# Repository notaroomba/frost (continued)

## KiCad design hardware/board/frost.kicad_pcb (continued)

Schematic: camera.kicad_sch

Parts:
C135: 1uF X5R 6.3V; C_0402_1005Metric
C136, C141, C142, C145, C146: 100nF X5R 10V; C_0402_1005Metric
C137: 22pF C0G 50V; C_0402_1005Metric
C138, C143, C144: 10uF X5R 10V; C_0603_1608Metric
C139, C140: 4.7uF X5R 6.3V; C_0603_1608Metric
C360, C361: 100nF X5R 10V; C_0201_0603Metric
R76: 10K 5%; R_0402_1005Metric
R77: 200K 1%; R_0402_1005Metric
R78: 390K 1%; R_0402_1005Metric
R79, R80, R81: 0R 5%; R_0402_1005Metric
U1: RK3568; BGA636C65P28X28_1900X1900X168; PARTREV 1.3; LCSC C3345225
U26: LP3983SAB5F-08; SOT-23-5_L3.0-W1.7-P0.95-LS2.8-BR; LCSC Part C324567
U27: 5054133410_C6422029; CONN-SMD_5054133410; LCSC Part C6422029

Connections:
CAM_CLKOUT0: U27.29
DVP_PWREN0_H_GPIO0_D3: R76.1; also elsewhere on the board
I2C2_SCL_M1: U27.31; also elsewhere on the board
I2C2_SDA_M1: U27.32; also elsewhere on the board
MIPI_AVDD_0V9: C360.1, U1.W14 (MIPI_CSI_RX_AVDD_0V9); also elsewhere on the board
MIPI_AVDD_1V8: C361.1, U1.Y14 (MIPI_CSI_RX_AVDD_1V8); also elsewhere on the board
MIPI_CAM0_RST_L_GPIO3_C6: R81.2; also elsewhere on the board
MIPI_CSI_RX_CLK0N: U1.AH10 (MIPI_CSI_RX_CLK0N), U27.10
MIPI_CSI_RX_CLK0P: U1.AG10 (MIPI_CSI_RX_CLK0P), U27.9
MIPI_CSI_RX_CLK1N: U1.AH9 (MIPI_CSI_RX_CLK1N)
MIPI_CSI_RX_CLK1P: U1.AG9 (MIPI_CSI_RX_CLK1P)
MIPI_CSI_RX_D0N: U1.AH12 (MIPI_CSI_RX_D0N), U27.7
MIPI_CSI_RX_D0P: U1.AG12 (MIPI_CSI_RX_D0P), U27.6
MIPI_CSI_RX_D1N: U1.AH11 (MIPI_CSI_RX_D1N), U27.13
MIPI_CSI_RX_D1P: U1.AG11 (MIPI_CSI_RX_D1P), U27.12
MIPI_CSI_RX_D2N: U1.AD11 (MIPI_CSI_RX_D2N), U27.4
MIPI_CSI_RX_D2P: U1.AE11 (MIPI_CSI_RX_D2P), U27.3
MIPI_CSI_RX_D3N: U1.AE9 (MIPI_CSI_RX_D3N), U27.16
MIPI_CSI_RX_D3P: U1.AD9 (MIPI_CSI_RX_D3P), U27.15
MIPI_CSI_X4_RST: C146.1, R81.1, U27.26
unnamed: C137.2, R77.1, R78.2, U26.4 (ADJ)
unnamed: C136.1, R76.2, U26.3 (CE)
VCC1V8_DOVDD_DVP: C139.1, C141.1, R79.1, U27.22
VCC2V8_AVDD_DVP: U27.23
VCC2V8_DVP: C140.1, C144.1, C145.1, R80.1, U27.24
VCC3V3_SYS: C135.1, U26.1 (VIN); also elsewhere on the board
VCCA1V8_IMAGE_P: R79.2; also elsewhere on the board
VDD1V2_DVDD_DVP: C137.1, C138.1, C142.1, C143.1, R77.2, U26.5 (VOUT), U27.21
VDDA0V9_IMAGE_P: R80.2; also elsewhere on the board

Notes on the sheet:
Frost
Camera MIPI Connector
RK3568
Diff 100 Ohm ±10%
Close to FPC Connector
NEEDS REWORKING TO ANOTHER STANDARD (JETSON NANO)
Power / Decoupling

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
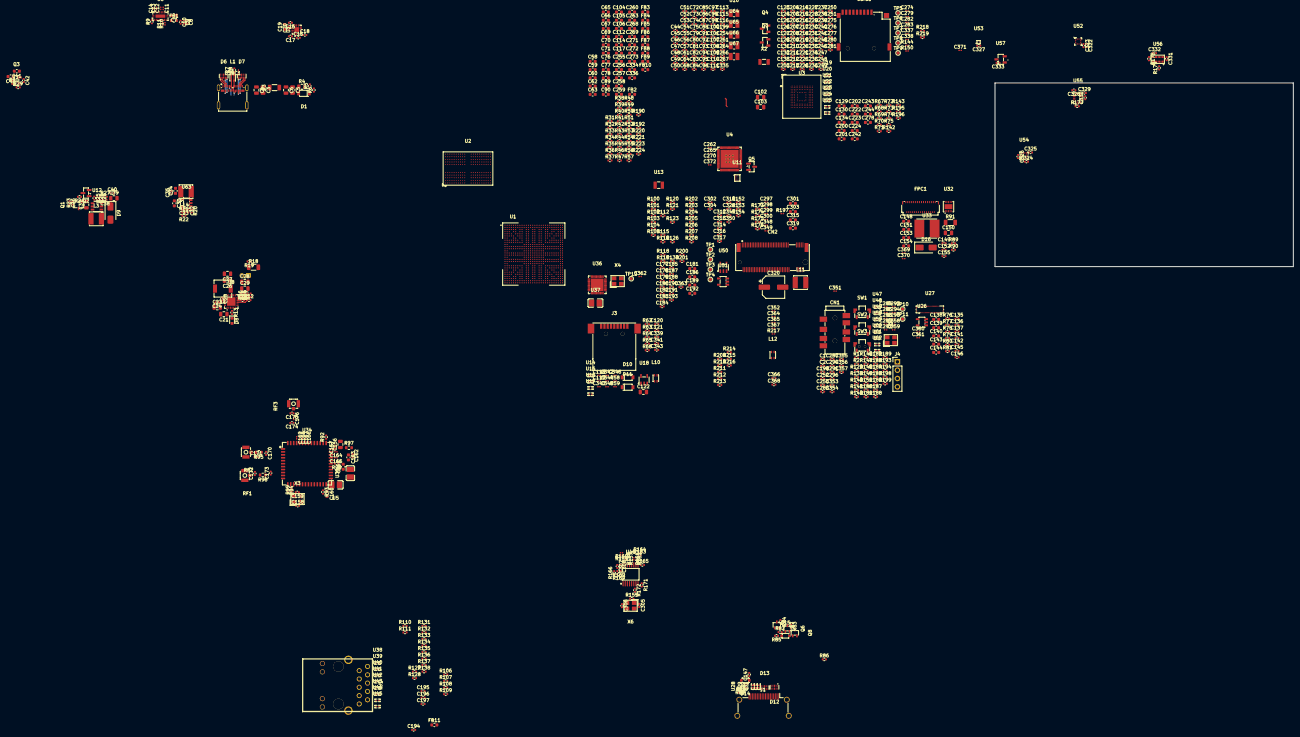
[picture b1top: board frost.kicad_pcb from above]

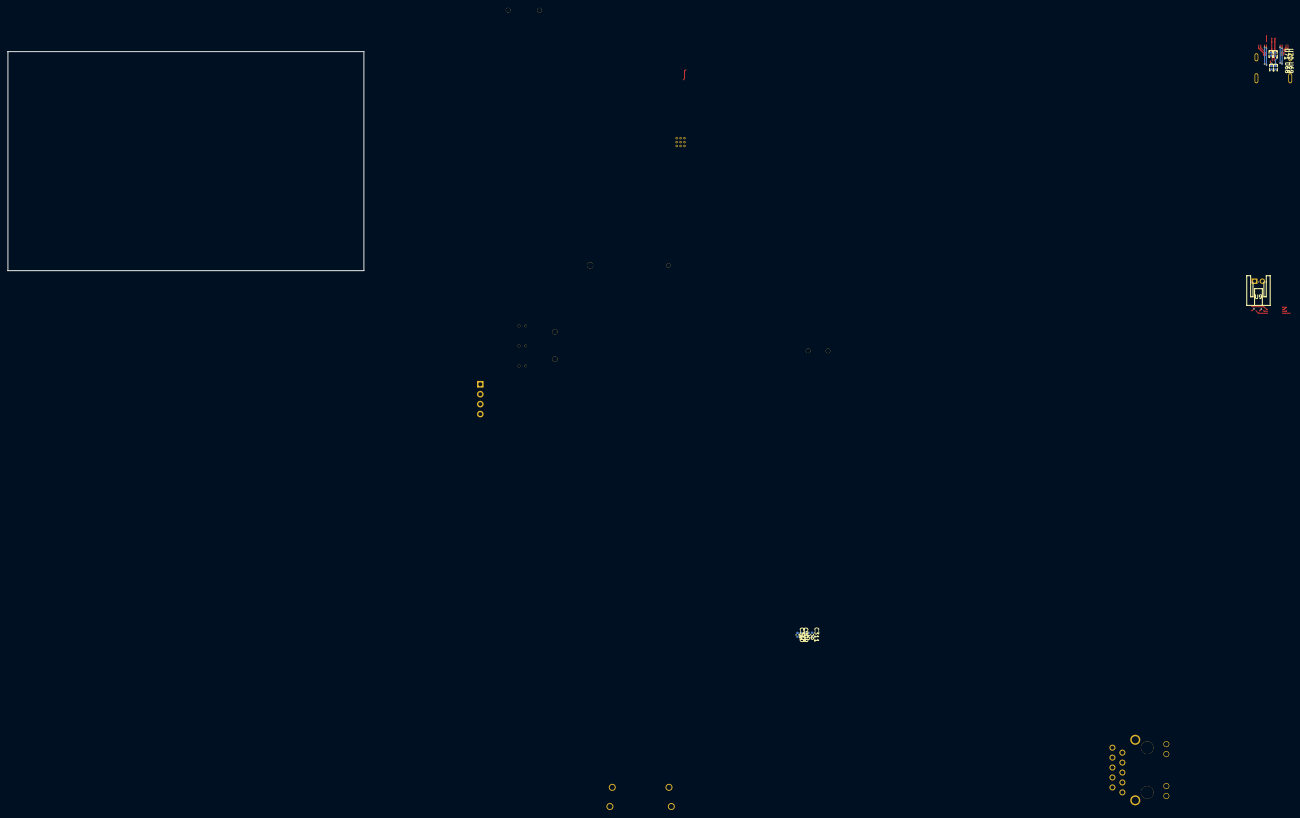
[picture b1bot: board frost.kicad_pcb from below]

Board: 6 copper layers, 91.0 x 56.0 mm, 726 parts (9 on the bottom side), 529 nets.

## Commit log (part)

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2025-12-03 init commit
2025-12-04 reading up on power
2025-12-07 added stuff
2025-12-07 added 3v3 buck and bat
2025-12-07 start pmic
2025-12-08 power done
2025-12-08 revised power
2025-12-09 emmc stuff
2025-12-10 MIPI IS FAKE
2025-12-11 change of camera
2025-12-14 start of ethernet
2025-12-14 finish ethernet
2026-03-15 add in pcie and ddr4
2026-03-15 aaaa
2026-03-15 sensors
2026-03-16 finished schematic!
2026-03-16 finished beautifying schematic
2026-03-25 did a thing
